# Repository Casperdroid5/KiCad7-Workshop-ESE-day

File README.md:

# KiCad Workshops

## Introduction Workshop:

Welcome to the KiCad introduction Workshop! This workshop is designed to provide you with the fundamental steps to kickstart your journey into printed circuit board (PCB) design using KiCad. Whether you're a beginner or have some experience, this workshop will equip you with the foundational knowledge and practical skills needed to design your own PCBs effectively.

### Workshop Topics:

1. **Downloading and Installation:**
   - Learn how to download and install KiCad on your Windows computer.

2. **Creating a New Project:**
   - Discover how to set up a new project, schematic, and organize your work efficiently.

3. **Adding Components:**
   - Learn to add electronic components to your schematic, arranging resistors, switches, LEDs, batteries, etc., in your design.

4. **Wiring Components:**
   - Guidance on connecting components with wires to ensure proper circuit connections.

5. **Assigning Footprints:**
   - Understand the association of real-world footprints with schematic symbols for accurate PCB design.

6. **Error Checking:**
   - Explore how to perform error checks to identify and resolve issues in your design.

7. **PCB Design:**
   - Introduction to PCB layout, transferring your schematic into a physical board effectively.

8. **Board Outline:**
   - Learn to create a board outline, defining the shape and dimensions of your PCB.

9. **Routing:**
   - Understand the process of routing connections on your PCB while adhering to good design practices.

10. **Final Review:**
    - Learn how to review your PCB design and visualize it in 3D to ensure it meets your project requirements.

### Outcome:
By the end of this workshop, you will have acquired the skills needed to begin designing functional and well-organized circuit boards for your projects.

## Advanced Workshop:

Ready to elevate your KiCad proficiency? The Advanced Workshop takes you deeper into advanced techniques and features in both the schematic and PCB editors.

### In Schematic Editor:

1. **Personalization:**
   - Add a personal touch by including your name on the schematic paper.

2. **Text Annotations:**
   - Utilize the text feature to include useful information, enhancing clarity and documentation.

3. **Advanced Schematic Organization:**
   - Master hierarchical sheets for a more organized and modular approach to complex designs.

4. **Netlabels:**
   - Use netlabels effectively to simplify and streamline schematic connections.

5. **Library Management:**
   - Explore importing components from external libraries for expanded options and design flexibility.

### In PCB Editor:

1. **Aesthetics and Customization:**
   - Learn to round off PCB corners for a professional look.

2. **Silkscreen Additions:**
   - Add a .bmp logo file and incorporate text for detailed PCB information.

3. **Symbolic Additions:**
   - Enhance the visual representation with useful symbols like polarity indicators.

4. **Advanced PCB Features:**
   - Create custom holes for unique features and add missing 3D models for a comprehensive view.

### Extra Enhancements:

1. **Library Integration:**
   - Explore parts/library integration for a broader range of electronic CAD symbols and models.

2. **KiCad Add-ons:**
   - Discover and leverage downloadable add-ons to enhance your KiCad experience according to your project requirements.

### Outcome:
By the end of this workshop, you'll be equipped with the skills to add personal touches to your designs, optimize your workflow, and incorporate advanced features for more professional-looking and functional PCBs.

Happy designing! 🚀

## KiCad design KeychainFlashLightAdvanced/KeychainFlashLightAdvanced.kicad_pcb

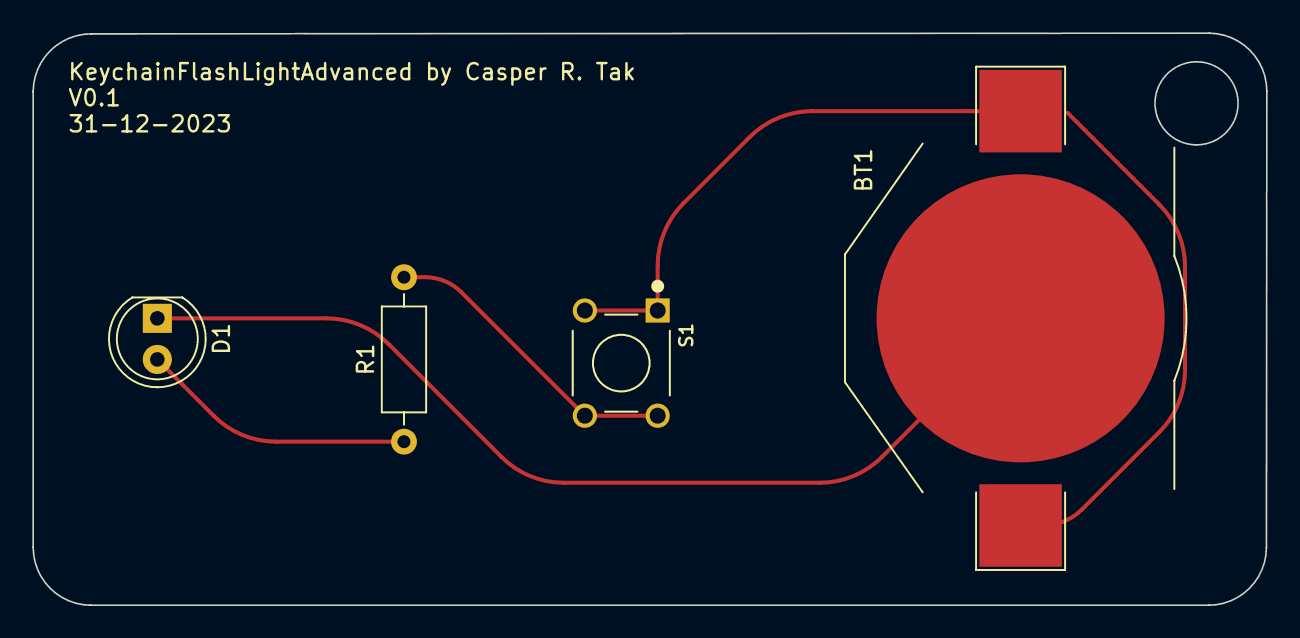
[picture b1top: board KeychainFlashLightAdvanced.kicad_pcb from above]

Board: 2 copper layers, 76.2 x 35.3 mm, 4 parts (0 on the bottom side), 3 nets.

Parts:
BT1: Battery_Cell; BatteryHolder_Keystone_3002_1x2032
D1: LED; LED_D5.0mm_Clear
R1: R; R_Axial_DIN0207_L6.3mm_D2.5mm_P10.16mm_Horizontal
S1: FSM8JH; SW_FSM8JH

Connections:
unnamed: BT1.1 (+), S1.1, S1.2
unnamed: D1.2 (A), R1.1
unnamed: R1.2, S1.3, S1.4

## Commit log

2023-08-22 added documentation
    first version of documentation (beginner)
2023-08-22 added KiCad design files
2023-08-22 added simple logo
2023-08-22 logo improved
    stretched logo
2023-11-30 added todo list
2023-11-30 added extra subjects to todo
2023-12-05 improved documentation Introduction workshop (former beginner)
2023-12-05 small documentation improvements and working on new schematic for Advanced workshop
2023-12-05 created setup for new document
2023-12-05 removed readme until next workshop completion
2023-12-05 removed garbage files
2023-12-05 cleanup
2023-12-30 Start on advanced PCB workshop
2023-12-30 added .bmp image for advanced workshop
2023-12-30 Added workshop components
    -Add information to the schematic page
    -Add informative text to the schematic sheet
    -Adding a hierarchical sheet
2023-12-30 minor improvements on documentation layout
2023-12-31 Workshop steps added
    Addition of:
    Step 4: Importing symbols,
    Step 5: Integrating the new button,
    Step 6: Redesigning the board outline and adding a hole,
    Step 7: Adding text and pictures to the PCB
2023-12-31 added step 7 to workshop
2023-12-31 Finished Advanced Workshop
2023-12-31 added pdf
2023-12-31 added readme and cleaned up
2023-12-31 updated missing 3d model
2024-01-03 added PowerPoint presentation and renamed files
2024-01-03 finished Presentation
2024-01-03 Improved presentation
2024-01-03 added production files
2024-01-08 Added "blanc" workshop files and cheatsheets
2024-01-08 renamed logo file
2024-01-08 renamed presentation
2024-01-18 minor textual improvement
2024-01-26 improvements added (dutch)
2024-01-28 Implemented feedback on introduction workshop
2024-01-28 Updated Advanced workshop, cleanup
    Both workshops now been updated with latest feedback
